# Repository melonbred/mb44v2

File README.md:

# MB-44 v2

## Introduction

The MB-44 is a 12.75u layout 0.5u blocker separating spacebars from the arrow cluster similar to typical 65% layout.

Version 2 is a refresh of the original project that ran in April 2021, updating the case and PCB design.

This repository includes resources for the PCB mainboard and switch plate for the MB-44 v2. Assets of the case are also available for render purposes only and are not intended for manufacturing.

## Improvements

The following are improvements made to the original MB-44:

- Effective key height (EKH) reduced from 24.6mm to 22.2mm
- PCB updated to STM32 from ATmega MCU.
- Updated from C3 variant of the Unified Daughter Board (UDB) to the S1 variant.
- PCB and bottom case cavity reduced to eliminate unnecessary reverberations.
- Brass interior cover plate and accent weight to provide some sound dampening and cover for the UDB cable.
- Plate mounting uses Geon's tadpoles.

## Keyboard Layout

## Information

Please note that users that would intend to use the resources in this repository is shall review all files prior to any sort of production or manufacturing. The author of this repository does not provide warranty and has no liability for how these resources are used.

Vial firmware has been compiled for for the PCB included in this repository. Firmware source is available [here](https://github.com/vial-kb/vial-qmk/tree/vial/keyboards/melonbred/mb44v2).

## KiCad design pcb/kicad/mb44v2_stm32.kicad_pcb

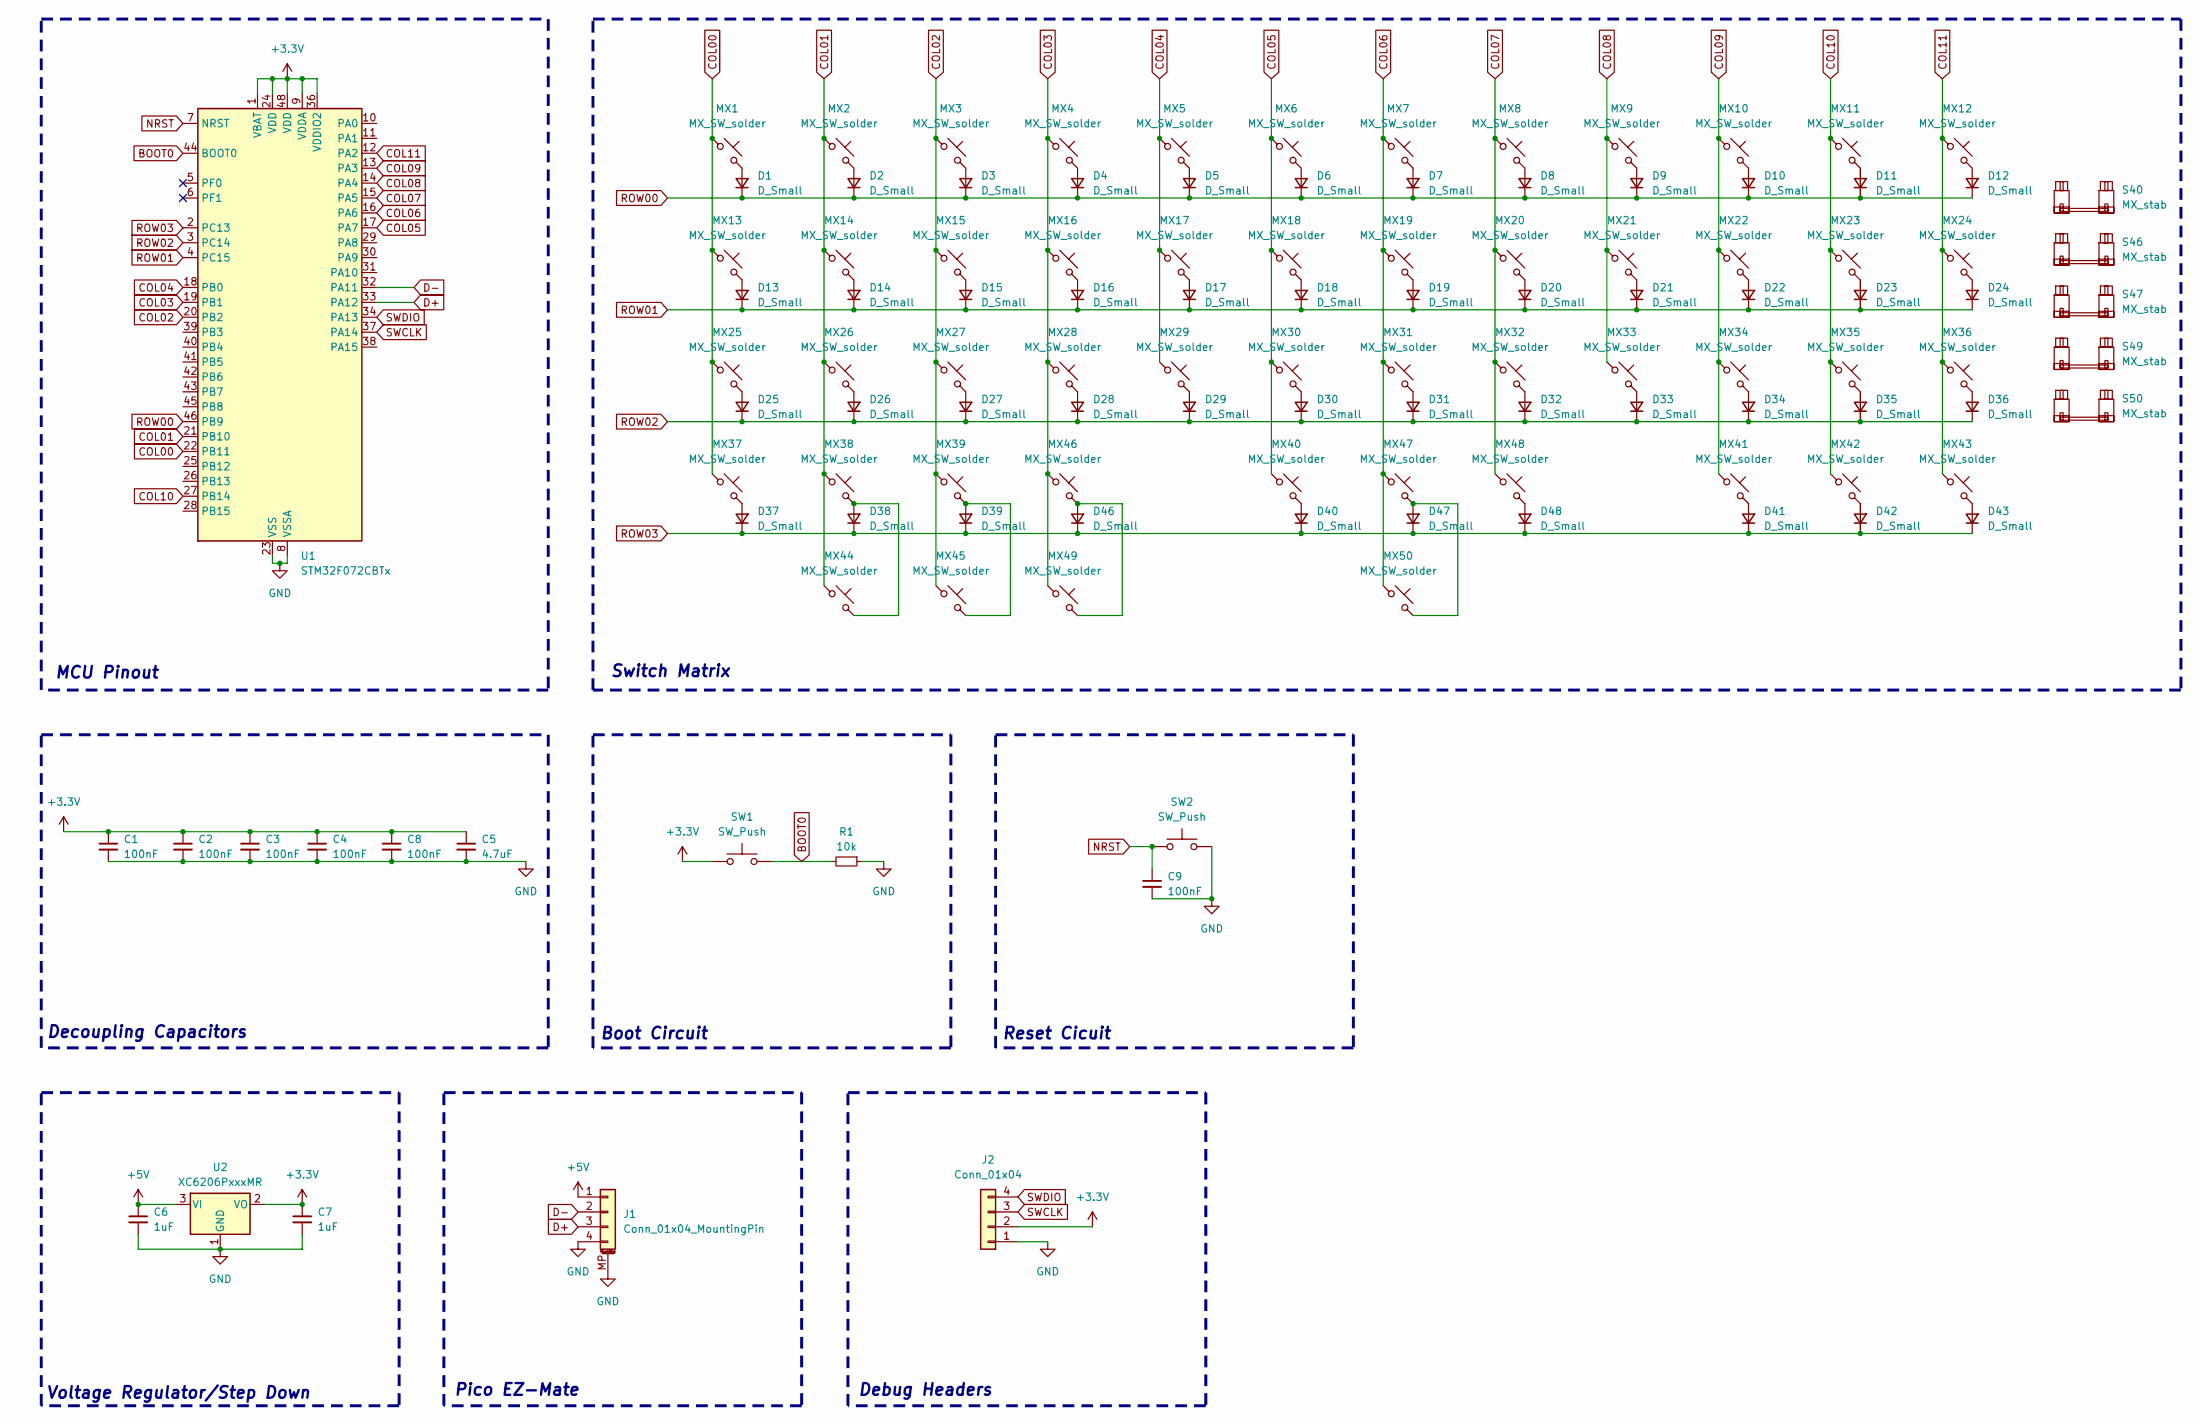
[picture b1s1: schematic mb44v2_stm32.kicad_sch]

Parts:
C1, C2, C3, C4, C8, C9: 100nF; C_0402_1005Metric; LCSC C307331
C5: 4.7uF; C_0402_1005Metric; LCSC C23733
C6, C7: 1uF; C_0402_1005Metric; LCSC C52923
D1, D2, D3, D4, D5, D6, D7, D8, D9, D10, D11, D12, D13, D14, D15, D16, D17, D18, D19, D20, D21, D22, D23, D24, D25, D26, D27, D28, D29, D30, D31, D32, D33, D34, D35, D36, D37, D38, D39, D40, D41, D42, D43, D46, D47: D_Small; D_SOD-523; LCSC Part C727112
D48: D_Small; D_SOD-523; LCSC C727112
J1: Conn_01x04_MountingPin; Molex_Pico-EZmate_78171-0004_1x04-1MP_P1.20mm_Vertical; LCSC C2997427
J2: Conn_01x04; PinHeader_1x04_P2.00mm_Vertical
MX1, MX2, MX3, MX4, MX5, MX6, MX7, MX8, MX9, MX10, MX11, MX14, MX15, MX16, MX17, MX18, MX19, MX20, MX21, MX22, MX23, MX26, MX27, MX28, MX29, MX30, MX31, MX32, MX33, MX34, MX35, MX36, MX37, MX38, MX39, MX40, MX41, MX42, MX43, MX45, MX46, MX47, MX48, MX49, MX50: MX_SW_solder; SW_MX_1u
MX12, MX25: MX_SW_solder; SW_MX_1.75u
MX13, MX44: MX_SW_solder; SW_MX_1.25u
MX24: MX_SW_solder; SW_MX_1.5u
R1: 10k; R_0402_1005Metric; LCSC C25744
S40: MX_stab; STAB_MX_P_6.25u
S46: MX_stab; STAB_MX_P_2.75u
S47: MX_stab; STAB_MX_P_2.25u
S49, S50: MX_stab; STAB_MX_P_3u
SW1, SW2: SW_Push; SW_SPST_SKQG_WithStem; LCSC C318884
U1: STM32F072CBTx; LQFP-48_7x7mm_P0.5mm; LCSC C81720
U2: XC6206PxxxMR; SOT-23-3; LCSC C5446

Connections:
+3.3V: C1.1, C2.1, C3.1, C4.1, C5.1, C7.1, C8.1, J2.2, SW1.1, U1.1 (VBAT), U1.9 (VDDA), U1.24 (VDD), U1.36 (VDDIO2), U1.48 (VDD), U2.2 (VO)
+5V: C6.1, J1.1, U2.3 (VI)
BOOT0: R1.2, SW1.2, U1.44 (BOOT0)
COL00: MX1.1, MX13.1, MX25.1, MX37.1, U1.22 (PB11)
COL01: MX2.1, MX14.1, MX26.1, MX38.1, MX44.1, U1.21 (PB10)
COL02: MX3.1, MX15.1, MX27.1, MX39.1, MX45.1, U1.20 (PB2)
COL03: MX4.1, MX16.1, MX28.1, MX46.1, MX49.1, U1.19 (PB1)
COL04: MX5.1, MX17.1, MX29.1, U1.18 (PB0)
COL05: MX6.1, MX18.1, MX30.1, MX40.1, U1.17 (PA7)
COL06: MX7.1, MX19.1, MX31.1, MX47.1, MX50.1, U1.16 (PA6)
COL07: MX8.1, MX20.1, MX32.1, MX48.1, U1.15 (PA5)
COL08: MX9.1, MX21.1, MX33.1, U1.14 (PA4)
COL09: MX10.1, MX22.1, MX34.1, MX41.1, U1.13 (PA3)
COL10: MX11.1, MX23.1, MX35.1, MX42.1, U1.27 (PB14)
COL11: MX12.1, MX24.1, MX36.1, MX43.1, U1.12 (PA2)
D+: J1.3, U1.33 (PA12)
D-: J1.2, U1.32 (PA11)
GND: C1.2, C2.2, C3.2, C4.2, C5.2, C6.2, C7.2, C8.2, C9.2, J1.4, J1.MP (MountPin), J2.1, R1.1, SW2.2, U1.8 (VSSA), U1.23 (VSS), U1.35 (VSS), U1.47 (VSS), U2.1 (GND)
NRST: C9.1, SW2.1, U1.7 (NRST)
unnamed: D1.2 (A), MX1.2
unnamed: D2.2 (A), MX2.2
unnamed: D3.2 (A), MX3.2
unnamed: D4.2 (A), MX4.2
unnamed: D5.2 (A), MX5.2
unnamed: D6.2 (A), MX6.2
unnamed: D7.2 (A), MX7.2
unnamed: D8.2 (A), MX8.2
unnamed: D9.2 (A), MX9.2
unnamed: D10.2 (A), MX10.2
unnamed: D11.2 (A), MX11.2
unnamed: D12.2 (A), MX12.2
unnamed: D13.2 (A), MX13.2
unnamed: D14.2 (A), MX14.2
unnamed: D15.2 (A), MX15.2
unnamed: D16.2 (A), MX16.2
unnamed: D17.2 (A), MX17.2
unnamed: D18.2 (A), MX18.2
unnamed: D19.2 (A), MX19.2
unnamed: D20.2 (A), MX20.2
unnamed: D21.2 (A), MX21.2
unnamed: D22.2 (A), MX22.2
unnamed: D23.2 (A), MX23.2
unnamed: D24.2 (A), MX24.2
unnamed: D25.2 (A), MX25.2
unnamed: D26.2 (A), MX26.2
unnamed: D27.2 (A), MX27.2
unnamed: D28.2 (A), MX28.2
unnamed: D29.2 (A), MX29.2
unnamed: D30.2 (A), MX30.2
unnamed: D31.2 (A), MX31.2
unnamed: D32.2 (A), MX32.2
unnamed: D33.2 (A), MX33.2
unnamed: D34.2 (A), MX34.2
unnamed: D35.2 (A), MX35.2
unnamed: D36.2 (A), MX36.2
unnamed: D37.2 (A), MX37.2
unnamed: D38.2 (A), MX38.2, MX44.2
unnamed: D39.2 (A), MX39.2, MX45.2
unnamed: D40.2 (A), MX40.2
unnamed: D41.2 (A), MX41.2
unnamed: D42.2 (A), MX42.2
unnamed: D43.2 (A), MX43.2
unnamed: D46.2 (A), MX46.2, MX49.2
unnamed: D47.2 (A), MX47.2, MX50.2
unnamed: D48.2 (A), MX48.2
ROW00: D1.1 (K), D2.1 (K), D3.1 (K), D4.1 (K), D5.1 (K), D6.1 (K), D7.1 (K), D8.1 (K), D9.1 (K), D10.1 (K), D11.1 (K), D12.1 (K), U1.46 (PB9)
ROW01: D13.1 (K), D14.1 (K), D15.1 (K), D16.1 (K), D17.1 (K), D18.1 (K), D19.1 (K), D20.1 (K), D21.1 (K), D22.1 (K), D23.1 (K), D24.1 (K), U1.4 (PC15)
ROW02: D25.1 (K), D26.1 (K), D27.1 (K), D28.1 (K), D29.1 (K), D30.1 (K), D31.1 (K), D32.1 (K), D33.1 (K), D34.1 (K), D35.1 (K), D36.1 (K), U1.3 (PC14)
ROW03: D37.1 (K), D38.1 (K), D39.1 (K), D40.1 (K), D41.1 (K), D42.1 (K), D43.1 (K), D46.1 (K), D47.1 (K), D48.1 (K), U1.2 (PC13)
SWCLK: J2.3, U1.37 (PA14)
SWDIO: J2.4, U1.34 (PA13)

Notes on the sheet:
Reset Cicuit
Debug Headers
Pico EZ-Mate
Voltage Regulator/Step Down
MCU Pinout
Switch Matrix
Boot Circuit
Decoupling Capacitors

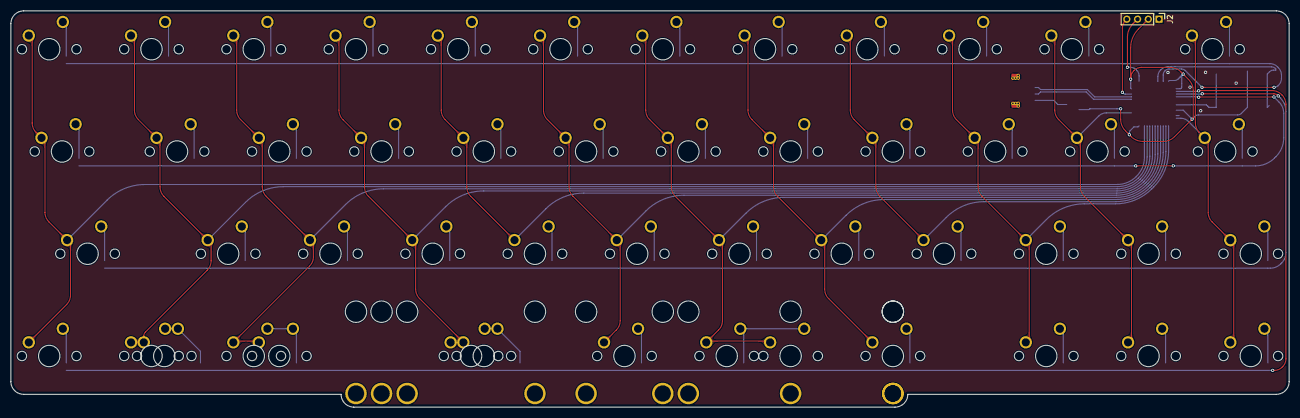
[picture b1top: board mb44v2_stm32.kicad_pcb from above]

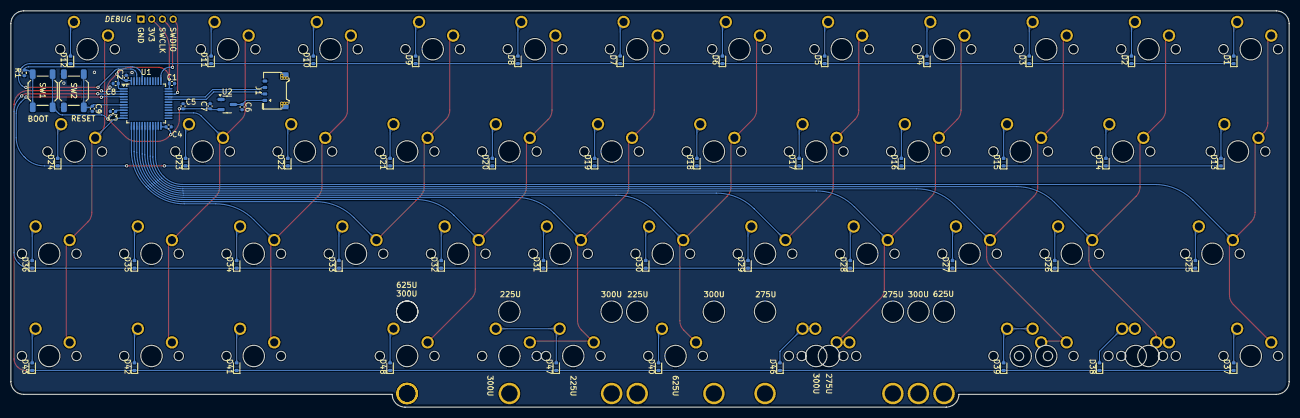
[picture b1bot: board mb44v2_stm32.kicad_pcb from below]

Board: 2 copper layers, 238.1 x 73.8 mm, 117 parts (61 on the bottom side), 71 nets.

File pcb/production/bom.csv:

Designator,Footprint,Quantity,Value,LCSC Part #
"C1, C2, C3, C4, C8, C9",402,6,100nF,C307331
C5,402,1,4.7uF,C23733
"C6, C7",402,2,1uF,C52923
"D1, D10, D11, D12, D13, D14, D15, D16, D17, D18, D19, D2, D20, D21, D22, D23, D24, D25, D26, D27, D28, D29, D3, D30, D31, D32, D33, D34, D35, D36, D37, D38, D39, D4, D40, D41, D42, D43, D46, D47, D48, D5, D6, D7, D8, D9",D_SOD-523,46,D_Small,C727112
J1,Molex_Pico-EZmate_78171-0004_1x04-1MP_P1.20mm_Vertical,1,Conn_01x04_MountingPin,C528030
R1,402,1,10k,C25744
"SW1, SW2",SW_SPST_SKQG_WithStem,2,SW_Push,C318884
U1,LQFP-48_7x7mm_P0.5mm,1,STM32F072CBTx,C81720
U2,SOT-23-3,1,XC6206PxxxMR,C5446

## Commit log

2026-03-03 Added position file for PCB production
